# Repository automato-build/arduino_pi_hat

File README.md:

# arduino_pi_serial HAT

#### TOP VIEW

#### BOTTOM VIEW

**Note:** _This is  part of a bigger project with automato.farm. This is just a small testing unit for some initial steps for next bigger ideas_

Assuming you are using [latest raspbian lite terminal only image](http://downloads.raspberrypi.org/raspbian/release_notes.txt) 
(we do not need GUI crap ATM).
Also assuming you have **updated**, **upgraded** and **set your locales** from the `raspi-config`. 

### CONFIGURE HARDWRAE SERIAL INTERFACE:
In `raspi-config`, under `interfaces` option **disbale console over serial** and then select **enable hardware serial**.

`sudo reboot`

Then run

`sudo ./setup_script.sh`

This sets fixes some setup

### A BIT ABOUT THE HARDWARE:
We are suing foot print of [Arduino Pro mini 3.3 V 8mHz](https://cdn.sparkfun.com/datasheets/Dev/Arduino/Boards/Arduino-Pro-Mini-v14.pdf) for the HAT in the schematic as PI's logic levels are all 3.3V. 

We are also providing some external 5 Volt supply for which we have created some back current 
and voltage surge protection circuit following the guidelines of Raspvbberry pi HAT [design guides](https://github.com/raspberrypi/hats/blob/master/designguide.md)

Also we have provided some Breakout GPIO pins for both Arduino and PI. (**Note**: _Not all the pins are broken out.You mighht need to solder few wires._)

We have also broken out ISP Ports for burning bootloader to ATMEga328. 
PLease [follow this guide](http://www.electronoobs.com/eng_arduino_tut6.php) here on how to do so. 
Only keep in mind few thing:
1. Use another Arduino Pro mini 3.3 V 8MHz as ISP programmer (folow the guide above on how to prepapre an Arduino for burning bootloader). Also use a 3.3 V logic enabled FTDI board for this master pro mini as pro minis do not have USB interface like pro micros. Don't forget to enable 3.3 V logic on it. Most boards have a jumper to switch between logic levels)

2. Also connect the ISP ports from this board (Will be marked on the baord) to the _MOSI_, _MISO_, _SCK_ and _CS_ pins of the programmer Arduino Pro mini. Rest follow the guide of burning bootloader.
3. Then you can use the same FTDI programmer  with the programming pads on the board to upload your code to the ATmega328.

In the design we have connected _PI's RX_ to Arduino's digital _pin 3_ and _PI's TX_ to Arduino's digital _pin 2_. We would be using **"SoftwareSerial"** lib on Arduino's side to confifure those pins as _software serial pins_ to establish serial communication with PI. This way we can keep the FTDI programmer attached to the programming pads on the baord to use Arduino's default Serial port for debugging the ATMega328.

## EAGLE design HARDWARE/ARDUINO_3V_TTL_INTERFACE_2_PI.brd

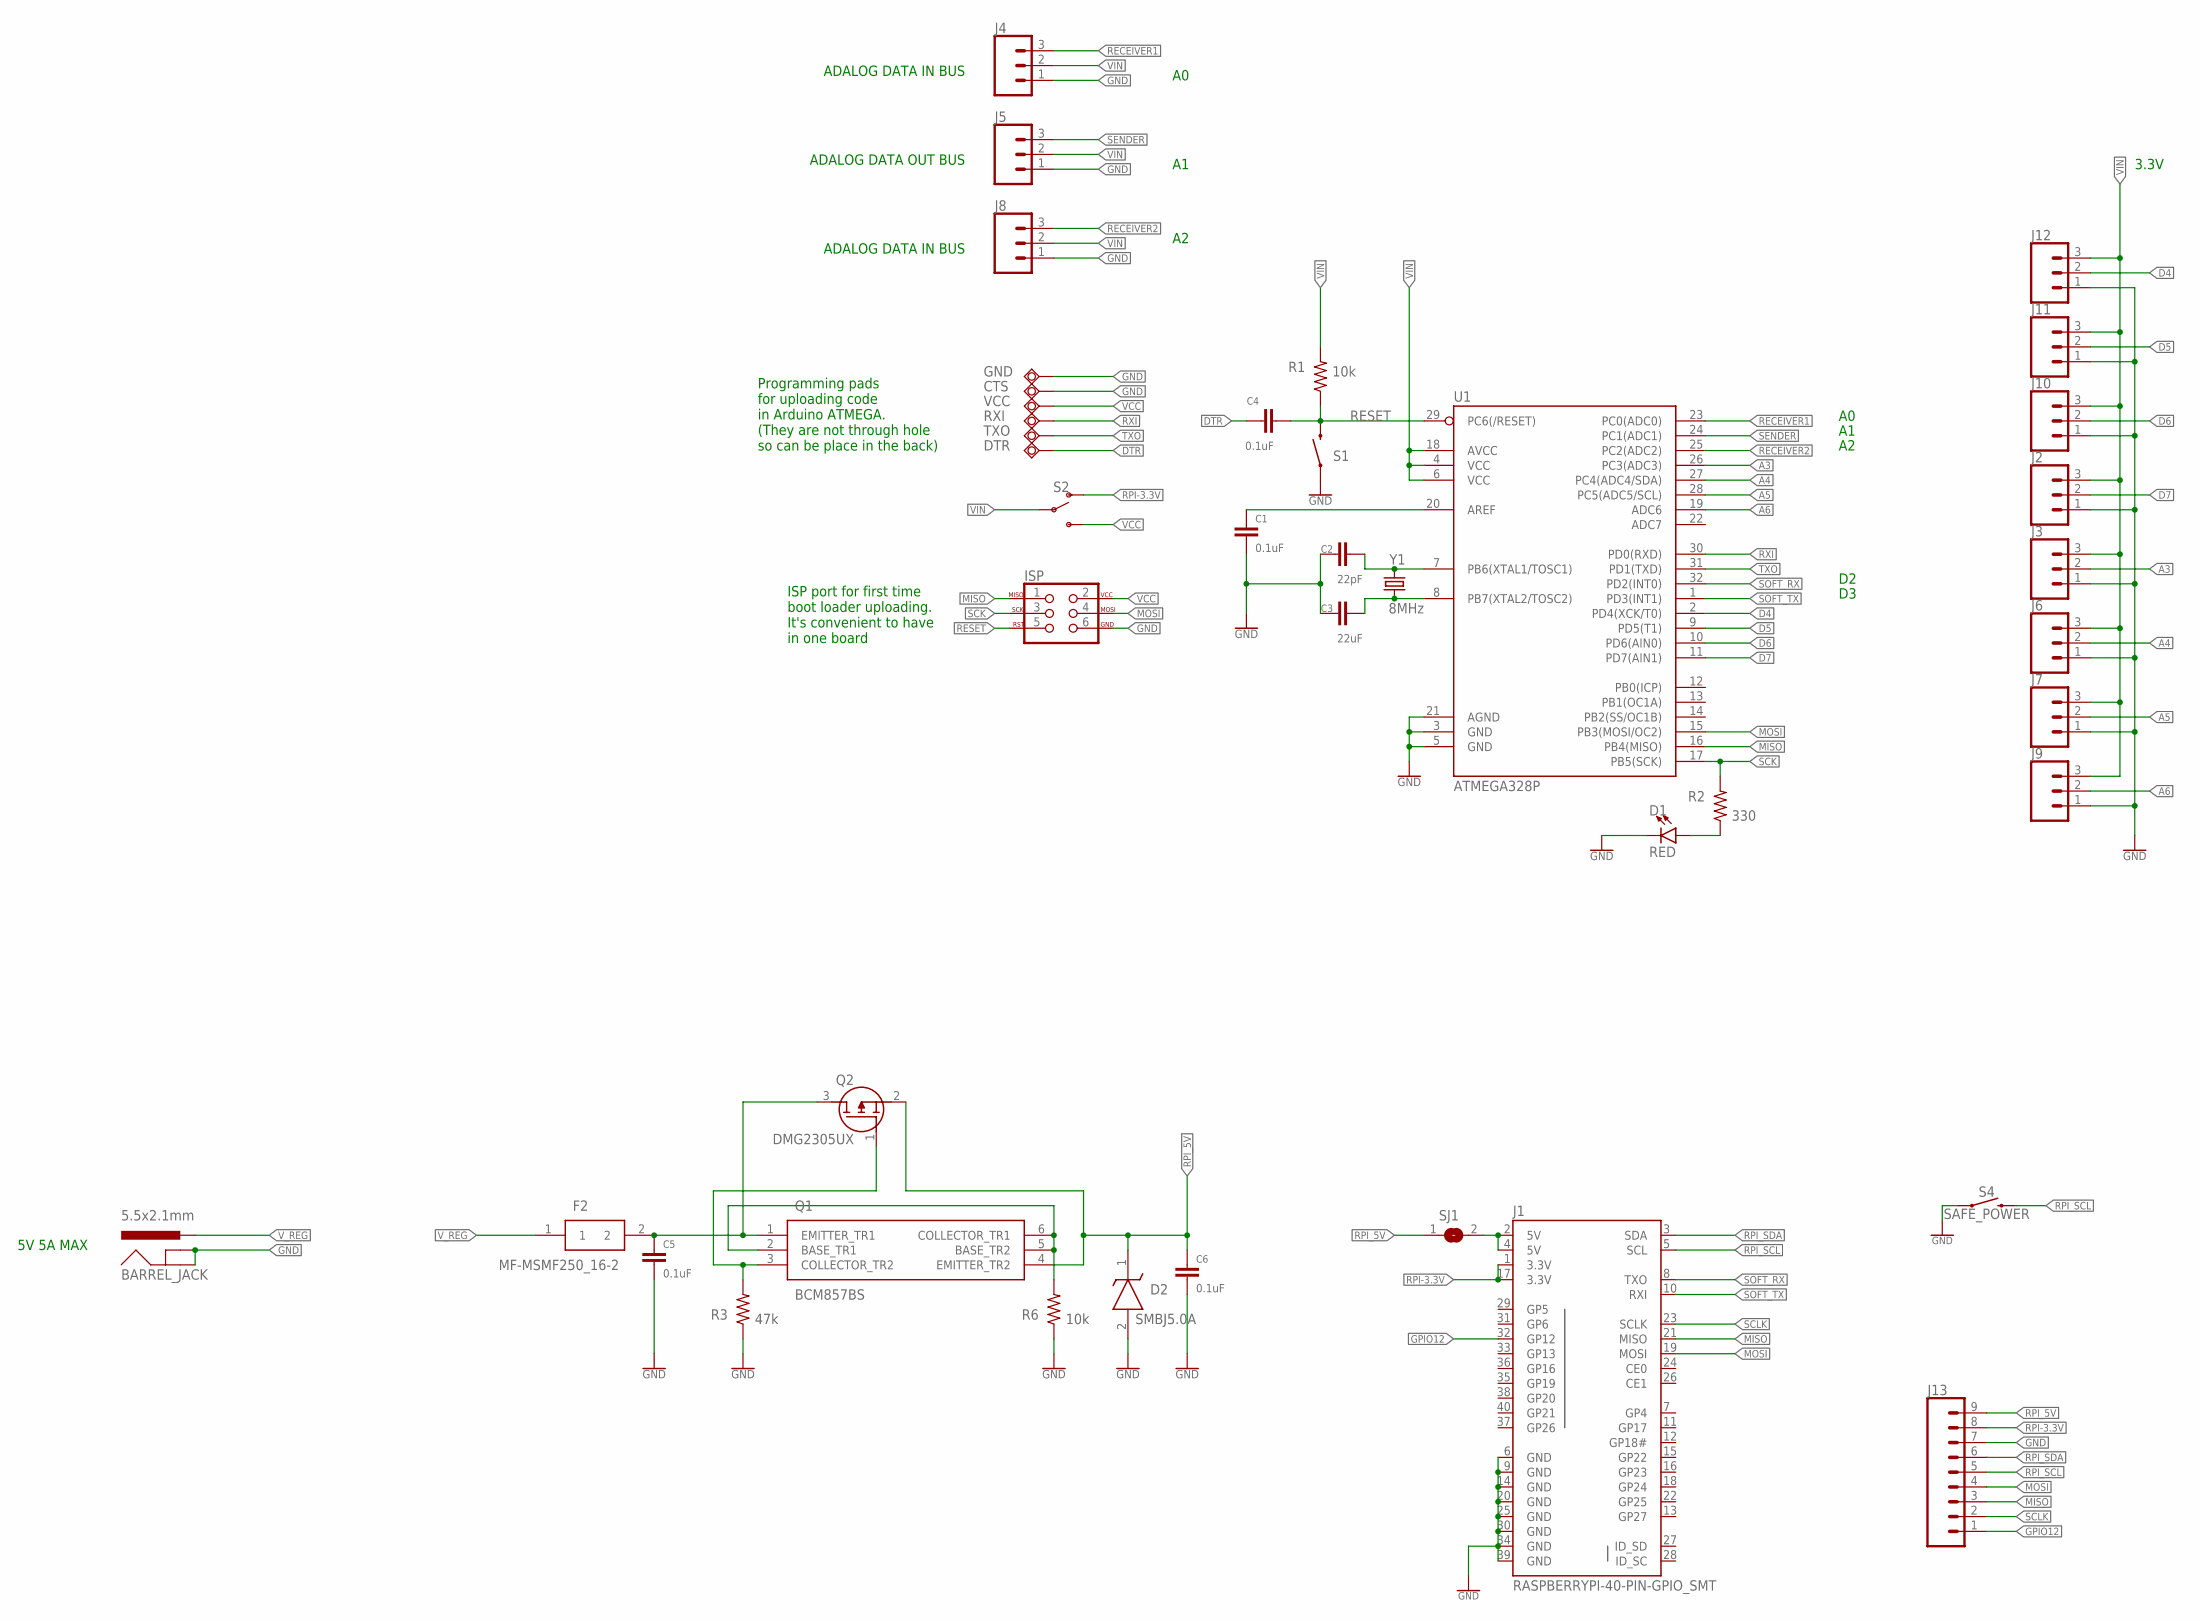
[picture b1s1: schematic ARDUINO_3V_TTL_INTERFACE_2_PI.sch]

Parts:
BARREL_JACK: 5.5x2.1mm; POWER_JACK_SMD
C1, C4, C5, C6: 0.1uF; 0603
C2: 22pF; 0603
C3: 22uF; 0603
CTS: TPSQB1,27; B1,27
D1: RED; LED-0603
D2: SMBJ5.0A; DIOM5436X244N
DTR: TPSQB1,27; B1,27
F2: MF-MSMF250_16-2; FUSC4632X160N
GND: TPSQB1,27; B1,27
ISP: AVR_SPI_PROG_3X2NS; 2X3-NS
J1: RASPBERRYPI-40-PIN-GPIO_SMT; 2X20_SHROUDED_SMT
J2, J3, J6, J7, J9, J10, J11, J12: CONN_03; 1X03
J4, J5, J8: CONN_03SMD; 1X03-1MM-RA
J13: CONN_09; 1X09
Q1: BCM857BS; SOT65P210X110-6N
Q2: DMG2305UX; SOT96P240X102-3N
R1, R6: 10k; 0603
R2: 330; 0603
R3: 47k; 0603
RXI: TPSQB1,27; B1,27
S1: RESET; TACTILE_SWITCH_SMD_4.6X2.8MM
S2: SWITCH-SPDT-SMD-RIGHT-ANGLE; SWITCH_SPST_SMD_A
S4: SAFE_POWER; TACTILE_SWITCH_PTH_12MM
SJ1: SJ
TXO: TPSQB1,27; B1,27
U1: ATMEGA328P; TQFP32-08
VCC: TPSQB1,27; B1,27
Y1: 8MHz; HC49UP

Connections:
A3: J3.2, U1.26 (PC3(ADC3))
A4: J6.2, U1.27 (PC4(ADC4/SDA))
A5: J7.2, U1.28 (PC5(ADC5/SCL))
A6: J9.2, U1.19 (ADC6)
D4: J12.2, U1.2 (PD4(XCK/T0))
D5: J11.2, U1.9 (PD5(T1))
D6: J10.2, U1.10 (PD6(AIN0))
D7: J2.2, U1.11 (PD7(AIN1))
DTR: C4.1, DTR.TP
GND: BARREL_JACK.GND (GNDBREAK), BARREL_JACK.P$4 (GND), C1.2, C2.1, C3.1, C5.2, C6.2, CTS.TP, D1.C, D2.2 (A), GND.TP, ISP.6, J1.6 (GND), J1.9 (GND), J1.14 (GND), J1.20 (GND), J1.25 (GND), J1.30 (GND), J1.34 (GND), J1.39 (GND), J2.1, J3.1, J4.1, J5.1, J6.1, J7.1, J8.1, J9.1, J10.1, J11.1, J12.1, J13.7, R3.1, R6.1, S1.1, S1.2 (1), S4.1, U1.3 (GND), U1.5 (GND), U1.21 (AGND)
GPIO12: J1.32 (GP12), J13.1
MISO: ISP.1, J1.21 (MISO), J13.3, U1.16 (PB4(MISO))
MOSI: ISP.4, J1.19 (MOSI), J13.4, U1.15 (PB3(MOSI/OC2))
unnamed: C1.1, U1.20 (AREF)
unnamed: J1.2 (5V), J1.4 (5V), SJ1.2
unnamed: D1.A, R2.1
unnamed: Q1.3 (COLLECTOR_TR2), Q2.1 (G), R3.2
unnamed: Q1.2 (BASE_TR1), Q1.5 (BASE_TR2), Q1.6 (COLLECTOR_TR1), R6.2
unnamed: C2.2, U1.7 (PB6(XTAL1/TOSC1)), Y1.2
unnamed: C3.2, U1.8 (PB7(XTAL2/TOSC2)), Y1.1
RECEIVER1: J4.3, U1.23 (PC0(ADC0))
RECEIVER2: J8.3, U1.25 (PC2(ADC2))
RESET: C4.2, ISP.5, R1.1, S1.3 (2), S1.4 (2), U1.29 (PC6(/RESET))
RPI-3.3V: J1.1 (3.3V), J1.17 (3.3V), J13.8, S2.1 (O)
RPI_5V: C6.1, D2.1 (K), J13.9, Q1.4 (EMITTER_TR2), Q2.2 (S), SJ1.1
RPI_SCL: J1.5 (SCL), J13.5, S4.3 (2)
RPI_SDA: J1.3 (SDA), J13.6
RXI: RXI.TP, U1.30 (PD0(RXD))
SCK: ISP.3, R2.2, U1.17 (PB5(SCK))
SCLK: J1.23 (SCLK), J13.2
SENDER: J5.3, U1.24 (PC1(ADC1))
SOFT_RX: J1.8 (TXO), U1.32 (PD2(INT0))
SOFT_TX: J1.10 (RXI), U1.1 (PD3(INT1))
TXO: TXO.TP, U1.31 (PD1(TXD))
VCC: ISP.2, S2.3 (S), VCC.TP
VIN: J2.3, J3.3, J4.2, J5.2, J6.3, J7.3, J8.2, J9.3, J10.3, J11.3, J12.3, R1.2, S2.2, U1.4 (VCC), U1.6 (VCC), U1.18 (AVCC)
V_REG: BARREL_JACK.VIN0 (PWR), C5.1, F2.1, F2.2, Q1.1 (EMITTER_TR1), Q2.3 (D)

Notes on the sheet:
ADALOG DATA IN BUS
ADALOG DATA OUT BUS
Programming pads for uploading code in Arduino ATMEGA. (They are not through hole so can be place in the back)
ISP port for first time boot loader uploading. It's convenient to have in one board
5V 5A MAX
3.3V

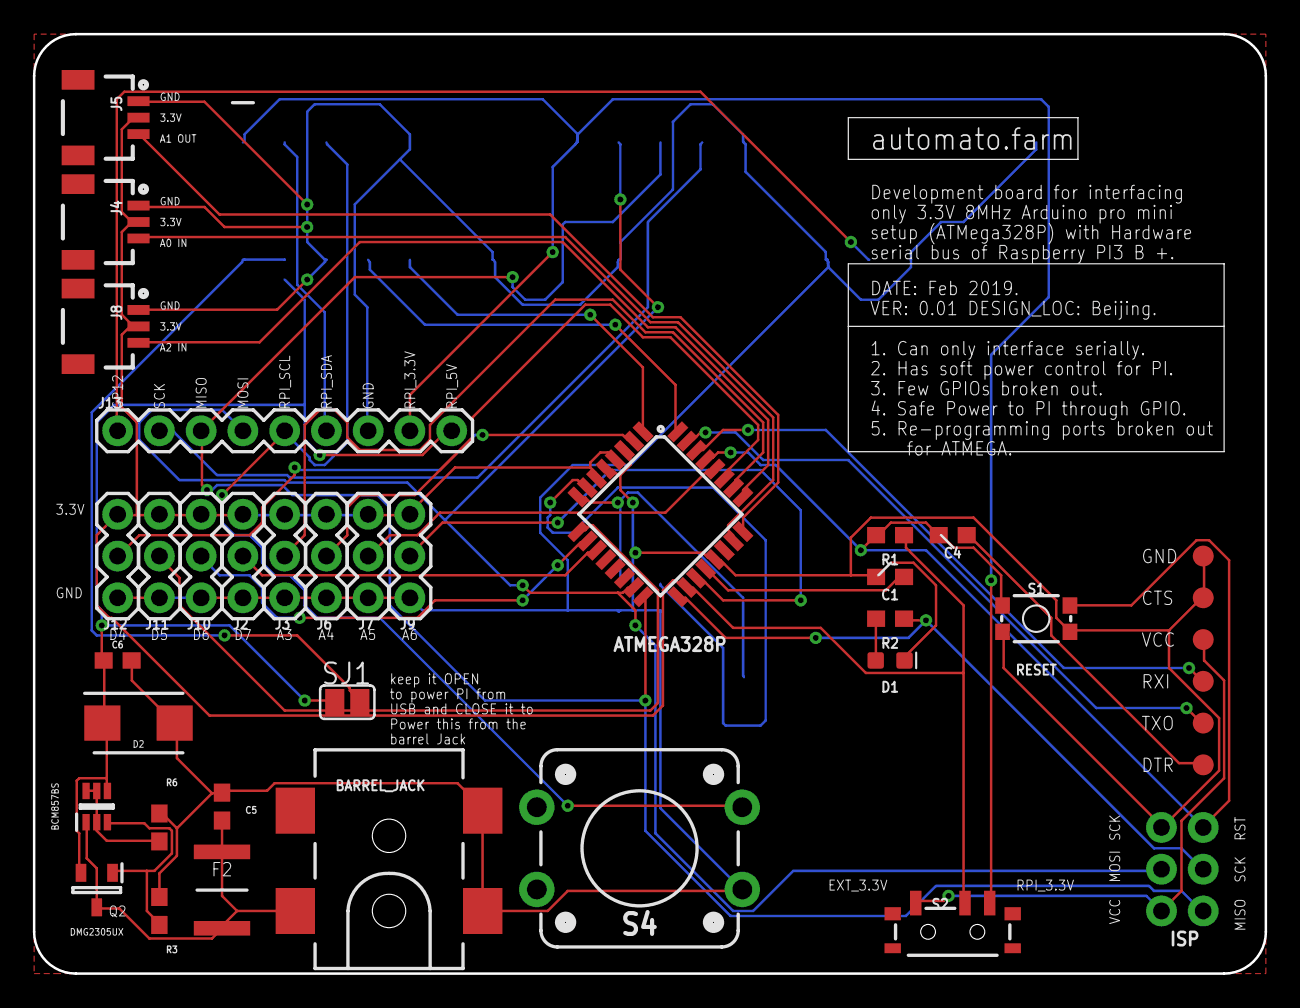
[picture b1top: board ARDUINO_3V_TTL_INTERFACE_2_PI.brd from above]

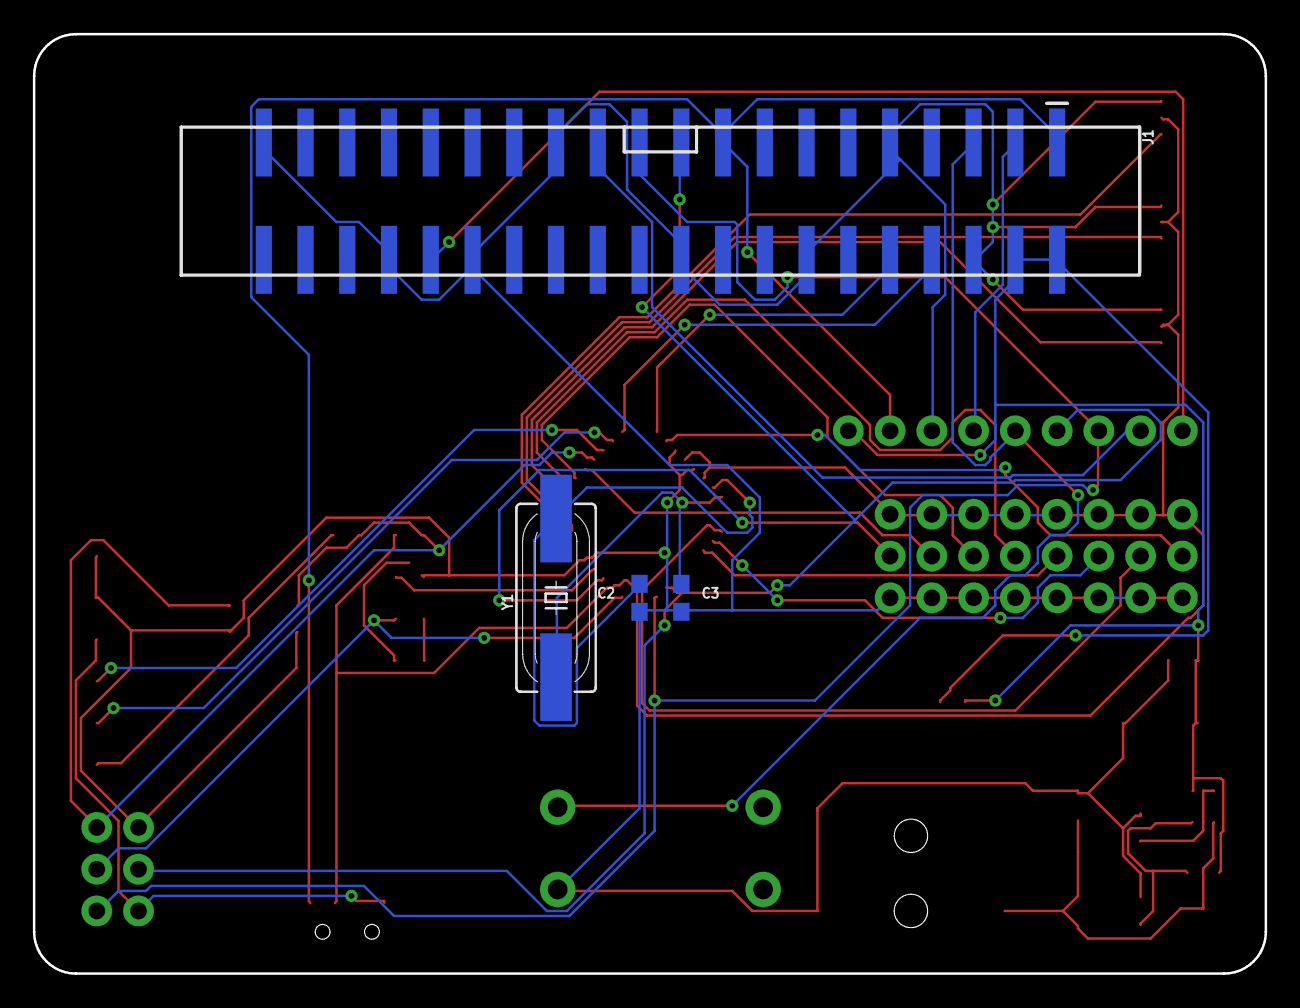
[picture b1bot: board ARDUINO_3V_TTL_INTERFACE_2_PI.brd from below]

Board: 2 copper layers, 74.9 x 57.1 mm, 42 parts (4 on the bottom side), 37 nets.

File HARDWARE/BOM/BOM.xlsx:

Part | Value | Quantity | Device | Package | Description | Buying Link
C1 | 0.1uF | 100 | 0.1UF-0603-100V-10% | 603 | 0.1µF ceramic capacitors | https://detail.tmall.com/item.htm?spm=a1z0d.6639537.19971966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
C2 | 22pF | 100 | 0.1UF-0603-100V-10% | 603 | 22pF ceramic capacitors | https://detail.tmall.com/item.htm?spm=a1z0d.6639537.19971966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
D1 | GREEN | 100 | LED-GREEN 0603 | LED-0603 | Green SMD LED | https://detail.tmall.com/item.htm?spm=a1z0d.6639537.19971966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
D5 | SMBJ5.0A | 30 | Uni-Directional TVS Diode SMBJ5.0A-E3_52 | DIOM5436X244N | Vishay SMBJ5.0A-E3/52, Uni-Directional TVS Diode, 600W, 2-Pin DO-214AA | https://item.taobao.com/item.htm?spm=a1z0d.6639537.199719660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
F2 | MF-MSMF250_16-2 | 30 | MF-MSMF250_16-2 | FUSC4632X160N | BOURNS - MF-MSMF250/16-2 - FUSE, RESETTABLE PTC, 16V, 2.5A, 1812 | https://detail.tmall.com/item.htm?spm=a230r.1.14.40.230d4481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
J1 | 40-PIN-GPIO_SMT (2x20) | 20 | RASPBERRYPI-40-PIN-GPIO_SMT | 2X20_SHROUDED_SMT | Raspberry Pi GPIO Header | https://item.taobao.com/item.htm?spm=a1z0d.6639537.199719660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
Q1 | BCM857BS | 20 | BCM857BS | SOT65P210X110-6N | NEXPERIA - BCM857BS - TRANSISTOR, MATCHED, SOT-363 | https://item.taobao.com/item.htm?spm=a1z0d.6639537.199719660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
Q2 | DMG2305UX | 20 | DMG2305UXQ-7 | SOT96P240X102-3N | MOSFET MOSFET BVDSS | https://detail.tmall.com/item.htm?spm=a1z0d.6639537.19971966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
R1 | 10k | 50 | 10KOHM-0603-1/10W-1% | 603 | 10K resistor | https://detail.tmall.com/item.htm?spm=a1z0d.6639537.19971966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
R2 | 330 | 50 | 10KOHM-0603-1/10W-1% | 603 | 330 resistor | https://detail.tmall.com/item.htm?spm=a1z0d.6639537.19971966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
R3 | 47k | 50 | 10KOHM-0603-1/10W-1% | 603 | 47K resistor | https://detail.tmall.com/item.htm?spm=a1z0d.6639537.19971966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
S2 | SPDT switch | 20 | SWITCH-SPDT-SMD-RIGHT-ANGLE | SWITCH_SPST_SMD_A | Single Pole, Double Throw (SPDT) Switch | https://item.taobao.com/item.htm?spm=a1z0d.6639537.199719660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
U1 | ATMEGA328P | 10 | ATMEGA328P_TQFP | TQFP32-08 | Popular 328P in QFP ATMega microcontroller | https://item.taobao.com/item.htm?spm=a1z0d.6639537.199719660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
Y1 | 8MHz | 20 | CRYSTAL-8M HZS MD-HC49UP | HC49UP | 8MHz Crystal | https://detail.tmall.com/item.htm?spm=a1z0d.6639537.19971966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
jst
barrel jack SMT
big push button
male headers

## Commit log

2019-02-20 added sample raspi side python serail scripts
2019-02-20 added a install script
2019-02-20 created README
2019-02-20 updating content in readme
2019-02-20 updating content of README
2019-02-20 updating readme
2019-02-20 sargagg
2019-02-20 sdrrfwert
2019-02-20 updating the README
2019-02-20 PCB's images
2019-02-20 added images
2019-02-21 checkiong migration to new profile
2019-02-21 added a jumper to separate ext voltage for testing it the volt reg citcuit doesn't work
2019-02-21 removed junk .test
2019-02-21 up-dated read me with new preview image including the new voltage separation jumper
2019-03-09 add lorenzo's pihat design

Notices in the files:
parts and their libraries:
SparkFun-Capacitors: Licensing: Creative Commons ShareAlike 4.0 International - https://creativecommons.org/licenses/by-sa/4.0
